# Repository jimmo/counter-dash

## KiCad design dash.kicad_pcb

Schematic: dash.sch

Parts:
AFF1: SBA23-11EGWA; 7SegmentLED_SBA23-11EGWA
C1, C2, C4: 100n; C_0805_HandSoldering
C3: 47u; C_Radial_D5_L11_P2
C5, C6: 22p; C_0805_HandSoldering
IC1: ATMEGA328-P; DIP-28_W7.62mm
P1: ICSP; Pin_Header_Straight_2x03
P2: ESP8266; Socket_Strip_Straight_2x04
P3: IN; Pin_Header_Angled_1x08
P4: OUT; Socket_Strip_Angled_1x08
P5: DC; Pin_Header_Straight_1x02
Q1, Q2: Q_NPN_CBE; TO-92_Inline_Narrow_Oval
Q3, Q4: Q_PMOS_GDS; TO-220_Neutral123_Vertical
R1: 680; Resistor_Vertical_RM5mm
R2: 220; Resistor_Vertical_RM5mm
R3, R8: 820; Resistor_Vertical_RM5mm
R4, R5, R6, R7, R11, R12: 10k; Resistor_Vertical_RM5mm
R9, R10: 4.7k; Resistor_Vertical_RM5mm
U1: LM317T; TO-220
U2: TLC5916; SOIC-16_3.9x9.9mm_Pitch1.27mm
Y1: 16MHz; Crystal_HC49-U_Vertical

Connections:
+12V: P5.1, Q3.3, Q4.3, R11.1, R12.1, U1.3 (IN)
EN_GREEN: IC1.5 ((PCINT19/OC2B/INT1)PD3), R10.1
EN_RED: IC1.4 ((PCINT18/INT0)PD2), R9.1
GND: C1.1, C2.1, C3.2, C4.2, C5.2, C6.2, IC1.8 (GND), IC1.22 (GND), P1.6, P2.8, P3.1, P4.1, P5.2, Q1.3, Q2.3, R1.1, R3.2, R8.1, U2.1 (GND), U2.13 (~OE)
unnamed: AFF1.2 (e), U2.9 (~OUT4)
unnamed: AFF1.3 (d), U2.8 (~OUT3)
unnamed: AFF1.4 (c), U2.7 (~OUT2)
unnamed: AFF1.6 (b), U2.6 (~OUT1)
unnamed: AFF1.7 (a), U2.5 (~OUT0)
unnamed: AFF1.8 (DP), U2.12 (~OUT7)
unnamed: AFF1.9 (f), U2.10 (~OUT5)
unnamed: AFF1.10 (g), U2.11 (~OUT6)
unnamed: C2.2, IC1.21 (AREF)
unnamed: C4.1, IC1.1 ((PCINT14/~RESET~)PC6), P1.5, R4.2
unnamed: C5.1, IC1.10 ((PCINT7/XTAL2/TOSC2)PB7), Y1.1
unnamed: C6.1, IC1.9 ((PCINT6/XTAL1/TOSC1)PB6), Y1.2
unnamed: IC1.2 ((PCINT16/RXD)PD0), P2.7
unnamed: IC1.3 ((PCINT17/TXD)PD1), P2.2
unnamed: IC1.16 ((PCINT2/OC1B/~SS~)PB2), P3.3, P4.3, U2.4 (LE)
unnamed: IC1.17 ((PCINT3/OC2A/MOSI)PB3), P1.4, P3.5, U2.2 (SDI)
unnamed: IC1.18 ((PCINT4/MISO)PB4), P1.1
unnamed: IC1.19 ((PCINT5/SCK)PB5), P1.3, P3.4, P4.4, U2.3 (CLK)
unnamed: P2.3, R5.1
unnamed: P2.4, R7.2
unnamed: P2.6, R6.2
unnamed: P3.8, P4.8
unnamed: P4.5, U2.14 (SDO)
unnamed: Q1.1, Q3.1, R11.2
unnamed: Q1.2, R9.2
unnamed: Q2.1, Q4.1, R12.2
unnamed: Q2.2, R10.2
unnamed: R1.2, R2.2, R3.1, U1.1 (ADJ)
unnamed: R8.2, U2.15 (R-EXT)
PWR_GREEN: AFF1.5 (CA_GREEN), P3.7, P4.7, Q4.2
PWR_RED: AFF1.1 (CA_RED), P3.6, P4.6, Q3.2
VCC: C1.2, C3.1, IC1.7 (VCC), IC1.20 (AVCC), P1.2, P2.1, P2.5, P3.2, P4.2, R2.1, R4.1, R5.2, R6.1, R7.1, U1.2 (OUT), U2.16 (VDD)

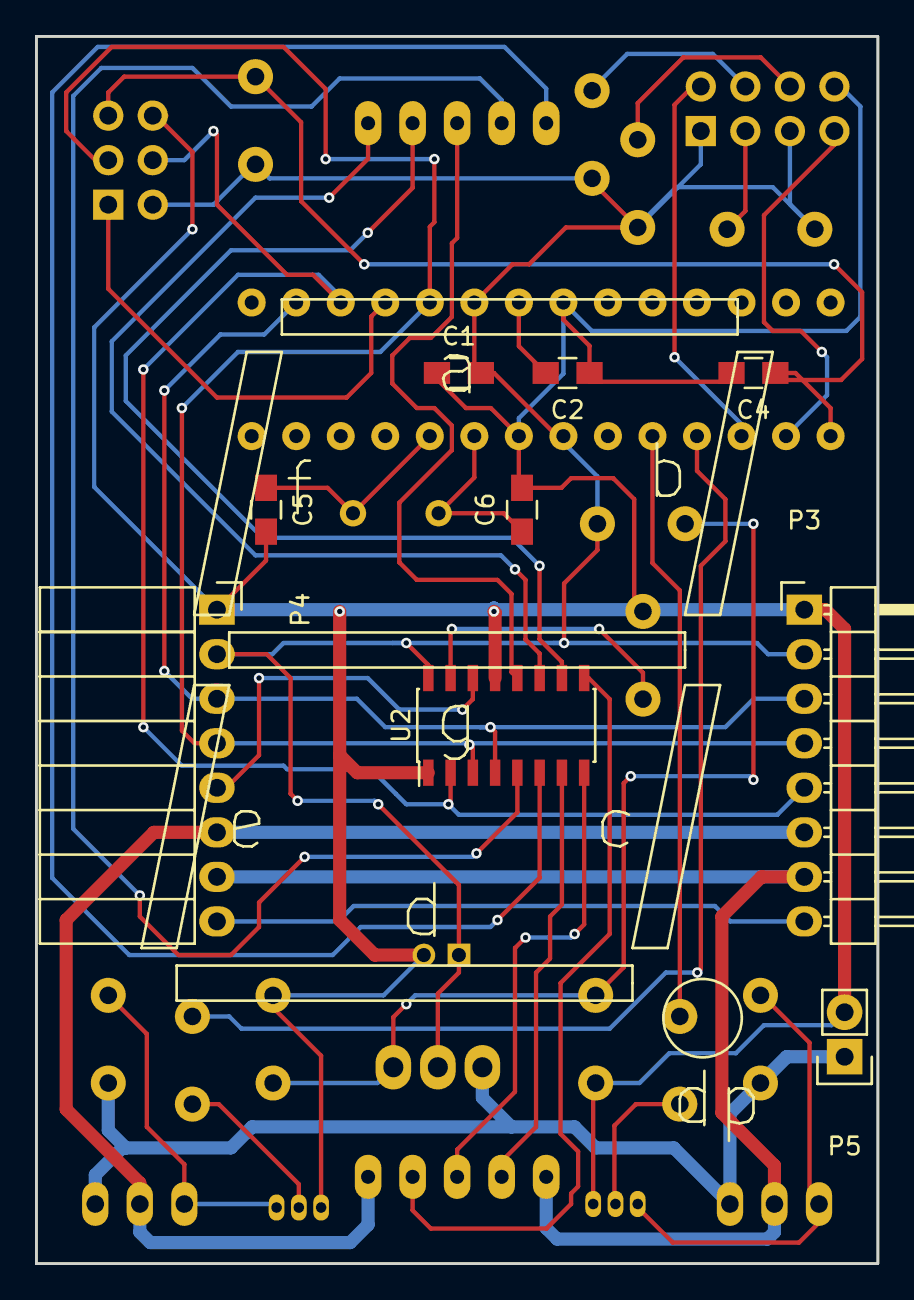
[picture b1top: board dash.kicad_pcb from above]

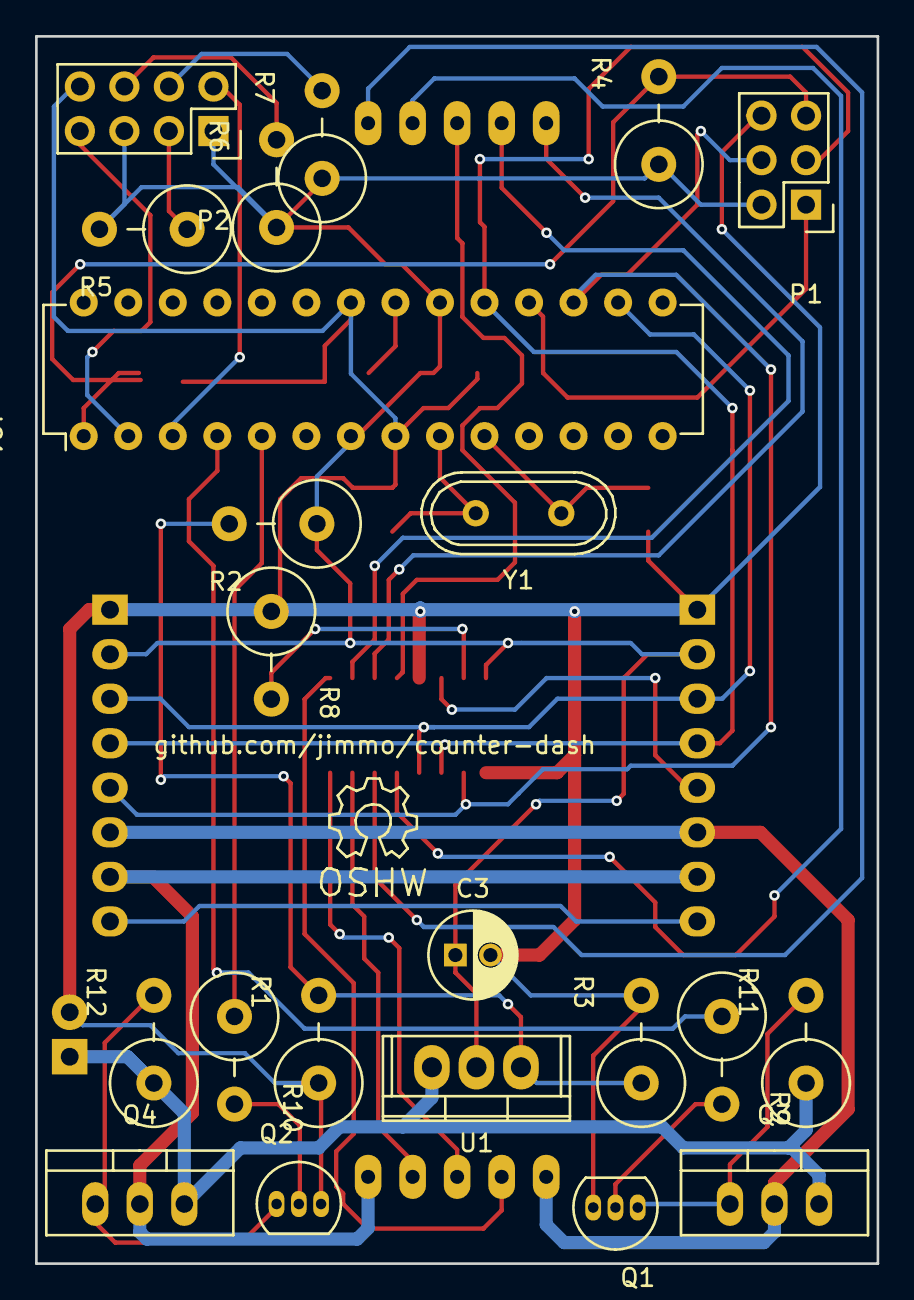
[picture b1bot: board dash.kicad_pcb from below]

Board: 2 copper layers, 48.0 x 70.0 mm, 33 parts (23 on the bottom side), 36 nets.

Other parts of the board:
github.com/jimmo/counter-dash: github.com/jimmo/counter-dash; Symbol_OSHW-Logo_SilkScreen

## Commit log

2016-07-25 Start some hand-routing.
2016-07-25 Finished routing. Still missing connection from +12 to red/green anode.
2016-07-25 First version. Mostly complete schematic.
2016-07-25 Start doing footprint assoc.
2016-07-25 Start re-routing new layout.
2016-07-25 More routing.
2016-07-25 Re-layout the PCB. vertical resistors, red/green supply mosfets.
2016-07-25 Finish routing second attempt.
2016-07-26 Re-orient the ESP8266 header.
2016-07-26 Change vias to 0.3mm
2016-08-03 Add basic firmware with wifi and led driving.
2016-08-04 hack hack hack it works! but the code is awful.
2016-08-05 Startup sequence.
2016-08-05 Add AP join.
2016-08-08 More fixes.
2017-01-02 Add python code for esp8266.
